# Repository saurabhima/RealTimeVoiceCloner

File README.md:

# RealTimeVoiceCloner

Real-time voice conversion for **Raspberry Pi**. Speech arrives from a **USB microphone**, is converted to a different speaking style/voice, and leaves through the **3.5 mm audio jack** into a phone for use in an active call. The same code runs on **Windows, Linux and macOS** for development.

```
USB mic ─► capture ─► noise gate ─► resample ─► [ backend ] ─► resample ─► limiter ─► jack ─► phone
 (48 kHz)   (PortAudio)              (soxr)     passthrough      (soxr)               (TRRS)
                                                 pitch (DSP)
                                                 onnx  (neural VC)
```

## Status
* Working, tested: audio engine, gate, resampling, limiter, streaming phase-vocoder pitch/voice changer, chunked streaming wrapper for neural models, CLI, offline `convert`, CI on 3 OSes + Pi-class ARM.
* **Neural voice cloning is a plug-in**: the `remote` backend (below) and the `onnx` backend runs your own exported model (contract in [docs/MODELS.md](docs/MODELS.md)). No model is bundled. The default `pitch` backend is a plain DSP voice changer, not a clone.
* Not yet validated on real Pi hardware / a real phone call; levels and latency need tuning on your setup.

## Neural cloning (kNN-VC, via a helper machine)
WavLM-Large (316M params) is far too heavy for live inference on a Pi, so the Pi keeps handling mic/jack and streams audio windows over TCP to a laptop/desktop (GPU optional) running the model:
```bash
# on the helper machine (any OS):  pip install -e ".[server]"
rtvc enroll --out alice.pt alice_*.wav                  # 16-bit PCM wavs of the target voice, ideally 5+ min
rtvc serve --runner knnvc --voice alice.pt --host 0.0.0.0 --port 9000
# on the Pi, set backend.name = "remote" and [backend.remote].host in your config
rtvc run -c configs/default.toml --backend remote --accept-responsible-use
```
* kNN-VC (Baas et al., 2023) swaps each source frame's WavLM features for the mean of its nearest frames in the target's bank, then vocodes with HiFi-GAN. No training; it only works with speech **you have consent to use**.
* `serve` loads the model via `torch.hub` from `bshall/knn-vc` (third-party code + weights from GitHub; review it first). Use `--hub /path/to/clone` for an offline copy.
* Fail-closed: if the server is slow or unreachable, the call hears **silence**, never your real voice.
* The link is **unauthenticated and unencrypted**: use a trusted LAN or an SSH/WireGuard tunnel, and keep `--host 127.0.0.1` unless needed.
* Latency ≈ chunk (200 ms) + crossfade + network + inference. Inference must stay under `chunk_ms`; the Pi log shows it.
* **Status:** transport, fail-closed behaviour, streaming wrapper and the kNN-VC `enroll` -> `serve` -> `convert` chain were run end to end (CPU only, synthetic test audio). Measured: a 0.6 s window (400 ms context + 200 ms chunk) took ~0.24 s on a CPU-only cloud container, i.e. slightly **slower than the 200 ms chunk**, so use a GPU or a fast desktop CPU, or raise `chunk_ms`. Voice quality on real speech is **not evaluated**. The server applies a smoothed auto-gain so converted speech tracks the input level (raw kNN-VC output was ~2x quieter than the input in my test); the default `output_gain_db = -12` then lowers it again for the phone's mic input, so calibrate with `rtvc tone`.
* Check your helper machine before a call: `rtvc bench --host <ip> --port 9000` times realistic windows and tells you whether it keeps up. On my CPU-only container: median 207 ms, p95 229 ms against a 200 ms budget, reported TOO SLOW.

## Responsible use
Only convert voices you have permission to use, and don't use this to deceive or defraud people on calls (impersonation can be illegal, and many jurisdictions and call-recording rules require disclosure). `rtvc run` refuses to start until you pass `--accept-responsible-use` or set `consent_acknowledged = true`.

## Hardware (Raspberry Pi → phone)
* **Pi 3B/3B+/4/400** have a 3.5 mm jack. **Pi 5 and Zero have none** — use a USB audio adapter with line-out instead (set `output_device` to its name).
* The jack is an *output only*. The phone's headset port expects a **TRRS** headset: earpiece on L/R, **microphone on the sleeve (CTIA)**. So the Pi's output must be wired to the phone's **mic** contact:
  1. Use a **TRRS breakout/adapter** (or a "headset-to-phone" cable). Connect Pi L+R (summed) → attenuator → DC-blocking capacitor (1–10 µF) → **mic** contact; grounds common.
  2. **Attenuate ~40 dB (≈100:1, e.g. 10 kΩ + 100 Ω divider).** Line level is ~1 Vpp; a phone mic input expects a few mV. Without this the call audio will be loud and distorted.
  3. The phone biases the mic line with ~2 V DC — the series capacitor protects the Pi. Never connect the Pi's 5 V/3.3 V to the phone.
* Phones without a jack: use the phone's USB-C/Lightning-to-3.5 mm adapter, which presents the same TRRS.
* Commercial "audio isolator / mic attenuator" cables are the easier route.
* Prefer a USB sound card for cleaner audio and fewer ground-loop hum problems; add a ground-loop isolator if you hear whine.

*System overview and wiring detail (values: 2 × 10 kΩ, 47 Ω, 2.2 kΩ, 4.7 µF; see `hardware/`). Not yet built or tested on real hardware, so verify with a multimeter and a low volume first.*

Prefer a single USB-C module (USB-C in, 3.5 mm jack out)? See **[USB-C Voice Module](hardware/usbc/README.md)** (design only, untested; pinout and support circuit from the C-Media datasheet and application notes; placement-only KiCad PCB in `hardware/usbc/pcb/`, not yet opened in KiCad).

Prefer one board? See the **[Voice HAT design](hardware/hat/README.md)** (CM108/CM119 module + attenuator + TRRS on a Pi-sized PCB; design only, untested).

## Using a USB audio adapter (recommended; required on Pi 5)
1. Plug in the USB mic and the USB audio adapter, then run `rtvc devices`. Both appear as USB devices; note each name.
2. Put a unique part of each name in `configs/default.toml`, e.g. `input_device = "Blue"` and `output_device = "USB Audio"`. Don't pick the same device for both unless it really is the mic.
3. Check `alsamixer` (F6 to select the card): unmute and set the adapter's playback volume to a fixed level, then leave it. Level changes after this should come from `output_gain_db`.
4. Wire the adapter's **headphone/line-out** through the attenuator and capacitor to the phone's TRRS mic contact (see Hardware). Many adapters output headphone-level audio (up to ~1 V), still far too hot for a phone mic: keep the ~40 dB attenuator.
5. Calibrate with `rtvc tone --output-gain-db -30` during a test call, then `rtvc run`.

Adapter notes: a mono-only adapter works (the engine falls back to mono); an adapter that has a combined 4-pole headset jack can be wired straight to a phone with a TRRS cable only if its output is attenuated and its mic contact is the one the phone expects (CTIA vs OMTP differ: if the far end hears nothing, try an OMTP/CTIA switch adapter).

## Install
### Raspberry Pi OS (64-bit Bookworm)
```bash
git clone https://github.com/saurabhima/RealTimeVoiceCloner && cd RealTimeVoiceCloner
./scripts/install_pi.sh
```
### Linux / macOS / Windows (development)
```bash
python -m venv .venv && source .venv/bin/activate     # Windows: .venv\Scripts\activate
pip install -e ".[dev]"        # add ,onnx for neural models
```
Linux needs `libportaudio2`; macOS/Windows wheels bundle PortAudio.

## Use
```bash
rtvc devices                                      # find your mic and output
rtvc convert in.wav out.wav --semitones 4         # offline test, no hardware
rtvc tone --output-gain-db -30                    # calibrate level into the phone
rtvc run -c configs/default.toml --accept-responsible-use
rtvc run --backend onnx -c my.toml                # neural model
```
Autostart on the Pi: `sudo systemctl enable --now rtvc`.

### Levels
Start with `output_gain_db = -12` plus the hardware attenuator, play `rtvc tone` while on a test call with a friend (or voicemail), and adjust until the far end hears a clean, undistorted tone. `rtvc run` prints processing time vs. the block budget, buffer under/overruns, and total latency.

### Latency
`block (20 ms) ×2 + backend`. Pitch backend ≈ 70 ms; neural chunk size dominates (≈ chunk + crossfade). Under ~250 ms total is comfortable for conversation.

## Layout
```
src/rtvc/dsp.py          gate, limiter, phase-vocoder pitch shifter
src/rtvc/pipeline.py     hardware-independent chain (unit-testable)
src/rtvc/audio_io.py     sounddevice engine, ring buffer, device lookup
src/rtvc/backends/       passthrough, pitch, chunked wrapper, onnx loader
configs/default.toml     all settings
scripts/                 Pi installer + systemd unit
```

## Roadmap
Formant-preserving shifting · built-in lightweight neural model (kNN-VC) · Bluetooth HFP/USB-gadget output for jack-less phones · web UI for live tuning.

MIT licensed.

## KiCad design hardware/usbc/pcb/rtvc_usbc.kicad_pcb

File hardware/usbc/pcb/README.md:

# RTVC USB-C Voice Module: KiCad PCB (placement only, not routed)

| File | What it is |
|---|---|
| `rtvc_usbc.kicad_pcb` | KiCad board: outline, all 33 footprints placed with nets assigned, GND pours on both layers, 37 GND stitching vias |
| `placement.csv` | Reference, x/y (mm), rotation and footprint for every part |

## Status: read before ordering anything
* **Placement only.** There are **no signal tracks**. In KiCad the 22 signal nets show as a ratsnest; route them with the interactive router. GND is handled by the two pours and the vias.
* **Never opened in KiCad.** I generated the file with the `kiutils` Python library (KiCad 6 file format, which KiCad 7/8/9 open and convert) and re-loaded it with the same library to confirm it parses. I could not run KiCad's DRC or view it in KiCad here. **Open it, press `B` to fill the zones, and run Design Rules Check before doing anything else.**
* **My own checks (not a KiCad DRC):** no overlapping courtyards, nothing outside the outline (except the two edge connectors, which overhang slightly on purpose), and no pad-to-pad gaps under 0.15 mm between different nets. The preview image comes from the same data.
* **Footprints are the official KiCad library parts** (`Package_QFP`, `Connector_USB`, `Connector_Audio`, `Resistor_SMD`, `Capacitor_SMD`, `Inductor_SMD`, `Package_TO_SOT_SMD`), so pad geometry is not hand-drawn. The KiCad libraries are CC BY-SA 4.0 with an exception that lets you use them in a design without share-alike; credit: KiCad Libraries.
* **Corrections this step caught in the earlier netlist:** the USB-C footprint names its pads `A1`, `B12`, `A4`, `B9`, ... separately (my earlier `A1B12`-style names did not exist), and the 3.5 mm jack I had picked (CUI SJ-3524) is a 3-pole stereo jack, not a 4-pole headset jack. The design now uses the 4-pole `PJ320D` footprint. The optional monitor socket (J3) was dropped; the phone-audio pads `T` and `R1` are simply left free.

## Board
* 2 layers, 48 x 29 mm rectangle (placeholder outline: shrink or shape it as you like).
* `J1` USB-C on the left edge, opening to the left. `J2` jack on the right edge, plug entering from the right. Check the connector and jack overhang against their datasheets and move the edge if needed: I aligned the nose of the jack to the board edge and the front of the USB-C to the left edge.
* `U1` (CM108B) is rotated 90 degrees so its USB pins (41, 42) face the connector, supply pins are on the top side, the headphone outputs (30, 32) on the top toward the attenuator, and the regulator pins (8, 9) on the bottom with their capacitors. Pin 1 is bottom-left.
* Rule of thumb from C-Media application note v1.5: keep the D+/D− pair short and together with no stubs over 200 mil, put each bypass cap right at its supply pin, and keep the analog (output, attenuator) area away from the USB traces.

## Things only you can check
1. The `PJ320D` contact mapping: I assumed `T` = tip, `R1` = ring 1, `R2` = ring 2, `S` = sleeve, so `S` carries the microphone signal and `R2` is ground (CTIA). Confirm against the jack's datasheet before ordering.
2. The VREF (pin 26) capacitor value flagged in the parent README.
3. Fab limits: the LQFP-48 has 0.5 mm pitch; check your PCB maker's minimum track/space and via sizes (vias here are 0.8 mm pad / 0.4 mm drill).
4. Add mounting holes, a proper outline, and a silkscreen if you want them.

## Rebuilding
The board is generated by a script (not included in this repo yet) from `../rtvc_usbc.net` and the official KiCad footprint libraries; the placement is in `placement.csv`.

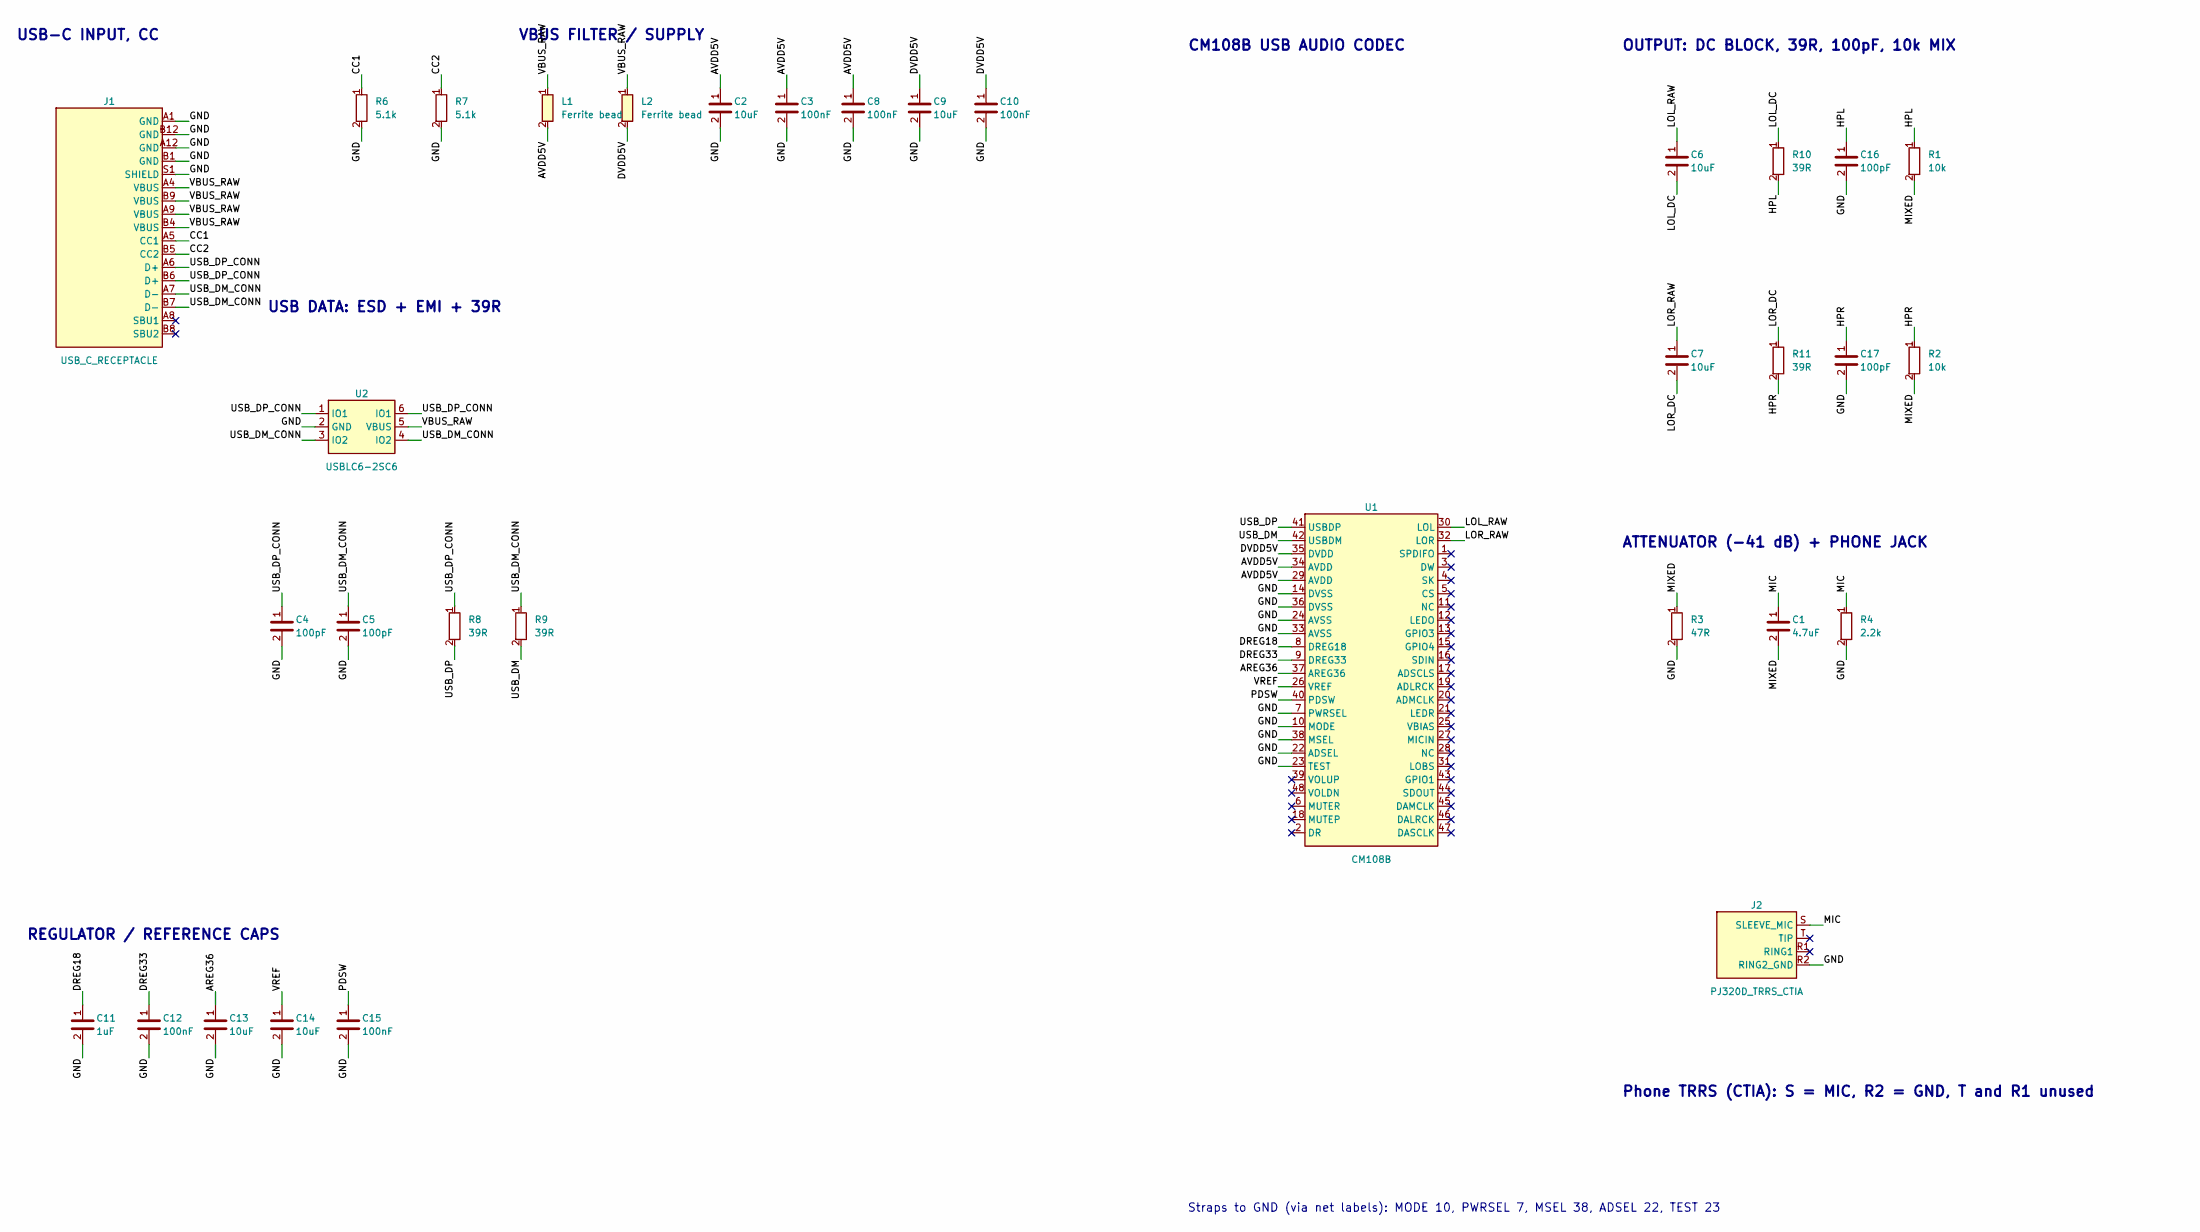
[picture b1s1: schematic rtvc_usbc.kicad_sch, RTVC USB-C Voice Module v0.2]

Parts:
C1: 4.7uF; C_0805_2012Metric
C2, C6, C7, C9, C13, C14: 10uF; C_0805_2012Metric
C3, C8, C10, C12, C15: 100nF; C_0603_1608Metric
C4, C5, C16, C17: 100pF; C_0603_1608Metric
C11: 1uF; C_0603_1608Metric
J1: USB_C_RECEPTACLE; USB_C_Receptacle_HRO_TYPE-C-31-M-12
J2: PJ320D_TRRS_CTIA; Jack_3.5mm_PJ320D_Horizontal
L1, L2: Ferrite bead; L_0805_2012Metric
R1, R2: 10k; R_0603_1608Metric
R3: 47R; R_0603_1608Metric
R4: 2.2k; R_0603_1608Metric
R6, R7: 5.1k; R_0603_1608Metric
R8, R9, R10, R11: 39R; R_0603_1608Metric
U1: CM108B; LQFP-48_7x7mm_P0.5mm
U2: USBLC6-2SC6; SOT-23-6

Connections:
AREG36: C13.1, U1.37 (AREG36)
AVDD5V: C2.1, C3.1, C8.1, L1.2, U1.29 (AVDD), U1.34 (AVDD)
CC1: J1.A5 (CC1), R6.1
CC2: J1.B5 (CC2), R7.1
DREG18: C11.1, U1.8 (DREG18)
DREG33: C12.1, U1.9 (DREG33)
DVDD5V: C9.1, C10.1, L2.2, U1.35 (DVDD)
GND: C2.2, C3.2, C4.2, C5.2, C8.2, C9.2, C10.2, C11.2, C12.2, C13.2, C14.2, C15.2, C16.2, C17.2, J1.A1 (GND), J1.A12 (GND), J1.B1 (GND), J1.B12 (GND), J1.S1 (SHIELD), J2.R2 (RING2_GND), R3.2, R4.2, R6.2, R7.2, U1.7 (PWRSEL), U1.10 (MODE), U1.14 (DVSS), U1.22 (ADSEL), U1.23 (TEST), U1.24 (AVSS), U1.33 (AVSS), U1.36 (DVSS), U1.38 (MSEL), U2.2 (GND)
HPL: C16.1, R1.1, R10.2
HPR: C17.1, R2.1, R11.2
LOL_DC: C6.2, R10.1
LOL_RAW: C6.1, U1.30 (LOL)
LOR_DC: C7.2, R11.1
LOR_RAW: C7.1, U1.32 (LOR)
MIC: C1.1, J2.S (SLEEVE_MIC), R4.1
MIXED: C1.2, R1.2, R2.2, R3.1
PDSW: C15.1, U1.40 (PDSW)
USB_DM: R9.2, U1.42 (USBDM)
USB_DM_CONN: C5.1, J1.A7 (D-), J1.B7 (D-), R9.1, U2.3 (IO2), U2.4 (IO2)
USB_DP: R8.2, U1.41 (USBDP)
USB_DP_CONN: C4.1, J1.A6 (D+), J1.B6 (D+), R8.1, U2.1 (IO1), U2.6 (IO1)
VBUS_RAW: J1.A4 (VBUS), J1.A9 (VBUS), J1.B4 (VBUS), J1.B9 (VBUS), L1.1, L2.1, U2.5 (VBUS)
VREF: C14.1, U1.26 (VREF)

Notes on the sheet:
USB-C INPUT, CC
VBUS FILTER / SUPPLY
USB DATA: ESD + EMI + 39R
REGULATOR / REFERENCE CAPS
CM108B USB AUDIO CODEC
OUTPUT: DC BLOCK, 39R, 100pF, 10k MIX
ATTENUATOR (-41 dB) + PHONE JACK
Phone TRRS (CTIA): S = MIC, R2 = GND, T and R1 unused
Straps to GND (via net labels): MODE 10, PWRSEL 7, MSEL 38, ADSEL 22, TEST 23

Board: 2 copper layers, 33 parts (0 on the bottom side), 23 nets, no tracks yet.

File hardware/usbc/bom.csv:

Ref,Qty,Value,Description,Footprint,Notes
J1,1,USB Type-C receptacle (USB 2.0 only),"16-pin mid-mount or top-mount","Connector_USB:USB_C_Receptacle_HRO_TYPE-C-31-M-12","Connect to the Pi with a USB-C to USB-A cable (Pi USB-C port is power-only)"
R6;R7,2,5.1k 1%,"CC pull-downs, 0603","Resistor_SMD:R_0603_1608Metric","CC1 and CC2 each to GND"
U2,1,USBLC6-2SC6,"USB ESD protection, SOT-23-6","Package_TO_SOT_SMD:SOT-23-6","Optional; at the connector side"
C4;C5,2,100pF,"Ceramic 0603","Capacitor_SMD:C_0603_1608Metric","D+ and D- to GND at the connector side (app note 3.5)"
R8;R9,2,39R,"Resistor 0603","Resistor_SMD:R_0603_1608Metric","USB D+/D- series (app note 3.5)"
L1;L2,2,Ferrite bead 0805,"Rated >=500 mA; value not given by C-Media (600R@100MHz typical)","Inductor_SMD:L_0805_2012Metric","VBUS to AVDD5V and to DVDD5V (separate)"
C2;C9,2,10uF 16V,"Ceramic 0805","Capacitor_SMD:C_0805_2012Metric","Bulk on AVDD5V and DVDD5V"
C3;C8;C10,3,100nF,"Ceramic 0603","Capacitor_SMD:C_0603_1608Metric","One at each supply pin: AVDD 34, AVDD 29, DVDD 35"
U1,1,CM108B,"C-Media USB audio codec, LQFP-48 7x7 mm","Package_QFP:LQFP-48_7x7mm_P0.5mm","Datasheet rev 1.11. Straps MODE/PWRSEL/MSEL/ADSEL/TEST to GND. CM119B is a related part: check its datasheet before substituting"
C11,1,1uF,"Ceramic 0603","Capacitor_SMD:C_0603_1608Metric","DREG18 pin 8 to GND (app note: 105)"
C12,1,100nF,"Ceramic 0603","Capacitor_SMD:C_0603_1608Metric","DREG33 pin 9 to GND (app note: 104)"
C13;C14,2,10uF 10V,"Ceramic 0805","Capacitor_SMD:C_0805_2012Metric","C13: AREG36 pin 37 (app note: 106). C14: VREF pin 26 (value from a figure with off-by-one pin labels: verify)"
C15,1,100nF,"Ceramic 0603","Capacitor_SMD:C_0603_1608Metric","PDSW pin 40 to GND (app note: 104)"
C6;C7,2,10uF 10V,"DC block, ceramic 0805","Capacitor_SMD:C_0805_2012Metric","LOL/LOR biased at 1.75 V. + toward U1 if polarised. Reference design uses 100uF for 32-ohm headphones"
R10;R11,2,39R,"Resistor 0603","Resistor_SMD:R_0603_1608Metric","Output series resistors (app note 3.2)"
C16;C17,2,100pF,"Ceramic 0603","Capacitor_SMD:C_0603_1608Metric","Output to GND (app note 3.2)"
R1;R2,2,10k,"Resistor 0603","Resistor_SMD:R_0603_1608Metric","L/R mix + divider series arm"
R3,1,47R,"Resistor 0603","Resistor_SMD:R_0603_1608Metric","Divider shunt (-41 dB total)"
R4,1,2.2k,"Resistor 0603","Resistor_SMD:R_0603_1608Metric","Mic-line DC load (headset detect)"
C1,1,4.7uF 16V,"Ceramic 0805 (non-polar) or electrolytic","Capacitor_SMD:C_0805_2012Metric","If polarised, + toward phone"
J2,1,PJ-320D (or equivalent) 3.5mm 4-pole jack,"SMD TRRS headset jack, pads S/T/R1/R2","Connector_Audio:Jack_3.5mm_PJ320D_Horizontal","Phone cable: 4-pole male-male TRRS, CTIA. Map S=MIC, R2=GND; T and R1 unused. Verify contact order against your jack datasheet"
-,1,USB-C to USB-A cable,"Module to Pi","","Short, USB 2.0 is enough"
-,1,TRRS male-male cable (CTIA),"Module to phone","","Or USB-C/Lightning-to-3.5 mm adapter if the phone has no jack"
-,1,PCB (2-layer),"Fabrication","","LQFP-48 0.5 mm pitch: needs hot-air or an assembly service"
